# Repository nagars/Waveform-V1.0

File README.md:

# Waveform-V1.0 (May 2018 - August 2018)

## IMPORTANT NOTE
### **This project is incomplete.** 
Though all the peripherals have been implemented and tested, I abandoned compiling them all into one homogenous project. At the time my intention
was to revisit the core design and implement a version 2.0. The reasons why have been listed further down. Effectively, the only features missing are:

- The ability to select the required waveform from a menu on the LCD using the encoder
- The ability to select frequency of the signal via the encoder. [Removed because it was causing signal integrity issues]

## Inspiration
Back in May of 2018, fresh out of college I decided to gain some experience on the PIC24 line of MCU's. Microchip has good hobbyists support through forums and documentation. 
But the biggest reason was that their MCU's come in DIP packaging which meant I could just use a breadboard for prototyping. 

**This would become my first major embedded systems project and my first time working with a PIC outside of college. It would also be my second PCB design on EagleCAD. 
Please bear that in mind if you want to use this for reference.**

## Table of Contents
1. Objective
    1. Feature List
    2. Knowledge Base Required
2. Design Breakdown
    1. PIC MCU
    2. Rotary Encoder
    3. DAC
    4. DMA
    5. LCD
    6. Negative Voltage Generator
    7. Opamp Stage
    8. Voltage Regulator
3. Issues
4. Media
5. Future Scope

## Objective
The objective of this project was to make a Waveform Generator based on a PIC24. Signals to be generated included SINE, SAWTOOTH, SQUARE and TRIANGLE. 
The device would have to include Frequency, Amplitude and DC Offset adjustment. It was to run on a 12V power supply.

### Feature List

- Device should run on 12V power supply with a DC jack
- LCD screen to show which signal has been selected
- Encoder to select signal via LCD
- Encoder to set Frequency of signal
- Pushbutton to enable / disable signal output (Included within Encoder)
- MCU Debug interface for on board debugging
- Resistor Ladder based DAC implementation
- Amplitude adjustment to max +-10V
- Frequency adjustment to max 1Mhz
- Offset adjustment to max +-10V
- Power switch and LED indicator

## Knowledge Base Required

- MPLAB IDE

    MPLAB is microchips IDE for PIC and now several AVR MCU's. It has all the standard IDE features including project management and Debugging. Microchip has it's own HAL
    called Harmony. I deliberately chose not to use it as I wanted a deeper understanding of the PIC's features.
      
- C programming language

    A basic understanding of c is necessary. How to use For loops, switch cases etc.
    
- Microcontroller basics

    A basic knowledge of how MCU's work, their hardware peripherals, working of interrupts and understanding of communication protocols is necessary. A major part of working with any MCU is understanding how to read and write to registers, access hardware etc.
      
- Analog Circuit Design / Analog Signals

    Knowledge regarding various signal types will be necessary. How Frequency, Ampitude and DC Offset affect a signal. How Opamps work, Thevenin and Norton theorem's, Linear regulators etc.
    
- EagleCAD

    EagleCAD is a what I designed the PCB in. It's popular among hobbyists because the free version is only limited by board size and not by the number of nodes as is with Orcad PCB Designer for example. It's a good place to start if you're looking to learn PCB designing.
    
    
## Design Breakdown
I will breakdown the software and hardware for each sub-system of my design.

Layout:

Schematic:

### PIC MCU
I used the [PIC24FJ64GA002](https://www.microchip.com/wwwproducts/en/PIC24FJ64GA002). Given the simple requirements of this project, almost any mainstream MCU will do.
Primarily I prioritised the following:

- Enough GPIO's (12 for the DAC, 3 for encoder inputs, 3 for the shift register, 2 for the LCD)
- 1 SPI (For the LCD)
- Fast speed (This one goes up to 32Mhz with an internal clock + PLL)
- DIP packaging to make a novice's life easier

## Rotary Encoder
I decided to use a relative rotary encoder with an internal pushbutton. The intention was to use the rotary encoder to select the signal type along with it's various parameters. The inputs would be finalised by pressing the encoder button. A good resource for encoders can be found [here](https://howtomechatronics.com/tutorials/arduino/rotary-encoder-works-use-arduino/).

The pushbutton along with the encoder outputs were driven to input GPIO's. I poll the encoder outputs using timer1 triggering an interrupt every 10ms. 

Since the encoder and its pushbutton are mechanical in nature, debouncing is necessary. This is because when a button is pressed, the metal plates make contact and tend to bounce on a microscopic level. This causes jitter or noise on the data line. This jitter can cause unpredictable behaviour as the signal jumps between the logic high and logic low thresholds of the gpio. To prevent this, there are several methods categorised as software and hardware debouncing. More information can be found [here](https://hackaday.com/2015/12/09/embed-with-elliot-debounce-your-noisy-buttons-part-i/). I chose to use hardware debouncing by implementing a simple rc filter to filter high frequency noise.

My code logic is simple. I read both outputs and place them into a single variable. The 0th and 1st bits represent each signal respectively. I enter a switch case where I compare the current configuration to the last polled one. Depending on which output has changed first, I determine if the encoder was rotated clockwise or counter-clockwise.

## DAC
DAC stands for **Digital to Analog Converter**. In short, it converts a digital number to an analog signal whose voltage varies depending on the value of said number. Say your DAC is 8 bits, it can handle numbers between 0 to 255. A value of 255 will output Vmax where as 128 will output 0.5*Vmax. 

I did not use the inbuilt DAC. I wanted to build my own using an R - 2R resistor ladder. There is no benefit to this, absolutely none but I did it anyway just to see how good or bad the results would be. You can find a good resource on it [here](https://www.electronics-tutorials.ws/combination/r-2r-dac.html).

Note: Most standard resistors have an error of between 10% to 1%. I ordered those with 0.1% error as the DAC is heavily dependent on equal values amongst its resistors. 

I decided to create a lookup table for the signals. It is an array of values that generate your signal on your DAC when you parse through the array. There are a bunch of tools to make lookup tables [like](https://www.daycounter.com/Calculators/Sine-Generator-Calculator.phtml).

I assigned the DAC pins to PORTB. Then I used the DMA module to transfer the array to PORTB. More information on that below. Depending on which gpio was set or cleared, the DAC put out a certain value between 0 and 5V. 

R - 2R DAC:

## DMA
DMA stands for **Direct Memory Access**. Basically it is an effective way of transfering data from one memory address to another, one peripheral to memory address or one memory address to a peripheral. Depending on the MCU, you may even transfer data from one peripheral to another. The advantage of using the DMA is that the processor has no role in this transfer. As a result it can go ahead and do other tasks without wasting time and resources on a memory transfer. The DMA runs independent of the processor.

I used the DMA to transfer 256 bytes from a specific lookup table address to the PORTB address. Upon completion, the DMA would trigger an interrupt where in I would trigger the same DMA transaction again resulting in a repeating signal generated at the DAC. 

There is a fundemental flaw in this method. How do you control the frequency of the signal? Instead of changing the rate of transfer to the DAC, I decided to reduce the number of data points of the signal to increase the frequency of the signal. So say for a 1 hz signal I would put out all 256 data points from the lookup table, to increase frequency I would reduce the number of data points. I did this by changing how I traverse the array. I would increase the number of elements to increment by. Thus, at higher frequencies the signal would be completely compromised. Even for a novice, this was a bad idea.

My plan now is to use a timer to trigger a single DMA transfer of 1 element in the array. With each trigger of the timer interrupt, I send out the next element to the port of the DAC. Now, I can control the frequency by adjusting the timer. I also found an [application note](http://ww1.microchip.com/downloads/en/Appnotes/00003312A.pdf) that does the same with the addded functionality of using a potentiometer to control the frequency.

 ## LCD
 I used a standard 16x2 LCD interfaced with a parallel port in 8 bit mode. The user would use the rotary encoder to select a highlighted option on the screen. A blinking option would mean you could change that options value. A good resource for interfacing an LCD like this can be found [here](https://circuitdigest.com/microcontroller-projects/16x2-lcd-interfacing-with-pic-microcontroller).
 
It uses an 8 bit parallel port for communication with the MCU. The PIC DIP package does not have enough gpio pins for that so I interfaced it with a 74HC595 shift register. The shift register takes a serial input which I interface with the SPI peripheral on the MCU. More information on shift registers can be found [here](https://lastminuteengineers.com/74hc595-shift-register-arduino-tutorial/).
  
LCD + Shift Register:

 ## Negative Voltage Generator
  The negative voltage generator circuit uses an IC555 Timer IC along with a configuration of Diodes and Capacitors to maintain a steady negative voltage of -12V at the output. 
  
  An IC555 timer is a common IC used to generate an oscillating signal. To do that, I use it in an Astable mode. By configuring the resistors and capacitors, I set my duty cycle to 50% with an oscillating frequency of 144Hz. This then feeds into the capacitor and diode setup. Detailed information on this can be found [here](https://www.allaboutcircuits.com/projects/build-your-own-negative-voltage-generator/).

-12V Generator:

 ## Opamp Stage
  I use the LM6178 opamp IC which comes with 2 opamps in an inverting amplifier configuration. The first Opamp stage is designed to offset and amplify the Analog signal coming from the DAC. This signal ranges from 0 to 5V. After the first opamp stage, the output signal is inverted and ranges from -0.5 to 0.5V. The second stage is designed to allow for user adjusted offset and amplitude using potentiometers. The output of the second stage can range from roughly -10V to 10V with an offset of +-10V.
  
Opamp Stage 1 & 2:

 ## Voltage Regulator
  I use the LM2576 5V buck converter to generate the 5V line to power the MCU, IC's and LCD. As a result the system has 3 power rails: 12V, -12V and 5V.

## Issues
Given that this was my first major project, a whole host of issues were expected.

1. Diode D1 overlaps the R - 2R ladder.
2. Diodes D2 and D3 do not fit in the space I provided on the board.
3. The power Jack is too large to fit on the board.
4. Higher frequencies result in the signal getting distorted. Issue is probably a combination of building my own DAC and of how I adjust the frequency in code explained above.
5. LCD used just looks plain awful hanging off the board.
6. Very very poor frequency control. 

## Media

Amplitude + Offset Adjustment: https://www.youtube.com/watch?v=x8Yp53ENj-I

Frequency Adjustment: https://www.youtube.com/watch?v=95g6IoSVtfY

## Future Scope
For now, this project is on pause. Between work, family and other projects I don't have any immediate plans to work on a version 2.0. However, the changes I will make when I get back to it will probably involve:

1. Replacing the PIC with an STM32. It's faster with clock going as far up as 40Mhz, it executes one instruction per cycle unlike the PIC with 2. The biggest factor
is the cost. The Pickit 4 debugger is around 7000 rs while an STM32 Nucleo evaluation board with the mcu and debugger is less than 2000 rs.

2. It goes without saying that I will switch to SMD parts to help with form factor. 

3. Finally, I'll abandon the R - 2R ladder and use the internal DAC of the MCU. Or maybe an external one with more bits. 

4. Implement an external oscillator for the MCU to avoid using a PLL.

5. Potentially implement digital potentiometers for signal adjustment.

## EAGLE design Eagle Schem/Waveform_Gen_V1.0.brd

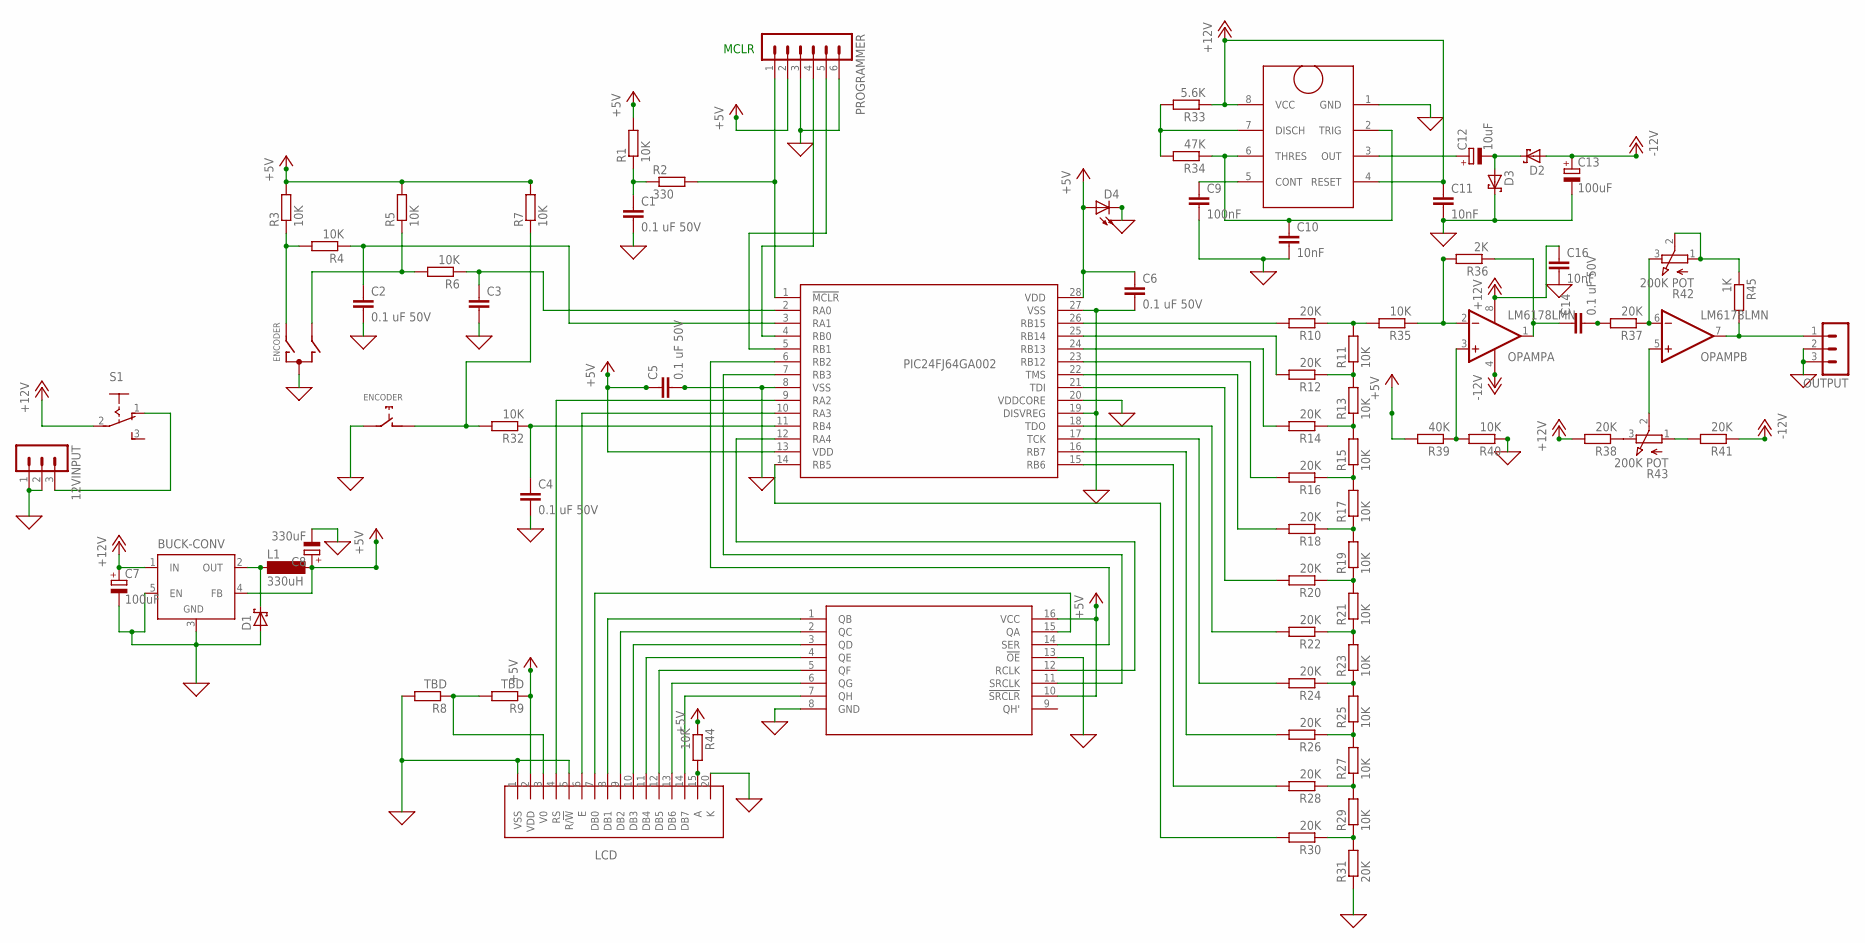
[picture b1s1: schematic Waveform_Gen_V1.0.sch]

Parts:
12VINPUT: MA03-1
BUCK-CONV: LM2596TH; TO220-52
C1, C2, C4, C5, C6, C14: 0.1 uF 50V; C5B2.5
C3: C5/2.5; C5B2.5
C7, C13: 100uF; E3,5-8
C8: 330uF; E3,5-10
C9: 100nF; C5B2.5
C10, C11, C16: 10nF; C5B2.5
C12: 10uF; E2,5-6E
D1, D2, D3: SCHOTTKY-DIODETO92H; TO92H
D4: SFH482
ENCODER: EC12E_SW; ALPS_EC12E_SW
IC555: IC555; DIL08
L1: 330uH; SD12K100
LCD: LCD_PIN; SIL16
OPAMP: LM6178LMN; DIL08
OUTPUT: MA03-1
PIC24FJ64GA002: PIC24FJ64GA002; DIL28-3
PROGRAMMER: MA06-1
R1, R3, R4, R5, R6, R7, R11, R13, R15, R17, R19, R21, R23, R25, R27, R29, R32, R35, R40, R44: 10K; 0207/10
R2: 330; 0207/10
R8, R9: TBD; 0207/10
R10, R12, R14, R16, R18, R20, R22, R24, R26, R28, R30, R31, R37, R38, R41: 20K; 0207/10
R33: 5.6K; 0207/10
R34: 47K; 0207/10
R36: 2K; 0207/10
R39: 40K; 0207/10
R42, R43: 200K POT; EVUF
R45: 1K; 0207/10
S1: 255SB
SHIFT-REG: 74HC595; DIL16

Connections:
+5V: BUCK-CONV.4 (FB), C5.1, C6.1, C8.+, D4.A, L1.2, LCD.2 (VDD), PIC24FJ64GA002.13 (VDD), PIC24FJ64GA002.28 (VDD), PROGRAMMER.2, R1.2, R3.2, R5.2, R7.2, R9.1, R39.2, R44.1, SHIFT-REG.10 (!SRCLR), SHIFT-REG.16 (VCC)
+12V: BUCK-CONV.1 (IN), C7.+, C11.1, C16.1, IC555.4 (RESET), IC555.8 (VCC), OPAMP.8 (V+), R33.1, R38.2, S1.2
-12V: C13.+, D2.1 (A), OPAMP.4 (V-), R41.1
GND: 12VINPUT.1, 12VINPUT.2, BUCK-CONV.3 (GND), BUCK-CONV.5 (EN), C1.2, C2.2, C3.2, C4.2, C5.2, C6.2, C7.-, C8.-, C9.2, C10.2, C11.2, C13.-, C16.2, D1.1 (A), D3.2 (C), D4.K (C), ENCODER.C, ENCODER.E (2), IC555.1 (GND), LCD.1 (VSS), LCD.5 (R/!W), LCD.20 (K), OUTPUT.2, OUTPUT.3, PIC24FJ64GA002.8 (VSS), PIC24FJ64GA002.19 (DISVREG), PIC24FJ64GA002.20 (VDDCORE), PIC24FJ64GA002.27 (VSS), PROGRAMMER.3, PROGRAMMER.6, R8.2, R31.1, R40.1, SHIFT-REG.8 (GND), SHIFT-REG.13 (!OE)
unnamed: PIC24FJ64GA002.7 (RB3), SHIFT-REG.11 (SRCLK)
unnamed: PIC24FJ64GA002.6 (RB2), SHIFT-REG.14 (SER)
unnamed: PIC24FJ64GA002.12 (RA4), SHIFT-REG.12 (RCLK)
unnamed: R42.1 (A), R42.2 (S), R45.1
unnamed: C3.1, PIC24FJ64GA002.2 (RA0), R6.1
unnamed: ENCODER.A, R3.1, R4.2
unnamed: PIC24FJ64GA002.1 (!MCLR), PROGRAMMER.1, R2.2
unnamed: C1.1, R1.1, R2.1
unnamed: ENCODER.D (1), R7.1, R32.2
unnamed: PIC24FJ64GA002.26 (RB15), R10.2
unnamed: C2.1, PIC24FJ64GA002.3 (RA1), R4.1
unnamed: ENCODER.B, R5.1, R6.2
unnamed: C4.1, PIC24FJ64GA002.11 (RB4), R32.1
unnamed: PIC24FJ64GA002.4 (RB0), PROGRAMMER.4
unnamed: PIC24FJ64GA002.5 (RB1), PROGRAMMER.5
unnamed: R10.1, R11.2, R35.2
unnamed: PIC24FJ64GA002.25 (RB14), R12.2
unnamed: R11.1, R12.1, R13.2
unnamed: R13.1, R14.1, R15.2
unnamed: R15.1, R16.1, R17.2
unnamed: R17.1, R18.1, R19.2
unnamed: R19.1, R20.1, R21.2
unnamed: R21.1, R22.1, R23.2
unnamed: R23.1, R24.1, R25.2
unnamed: R25.1, R26.1, R27.2
unnamed: R27.1, R28.1, R29.2
unnamed: R29.1, R30.1, R31.2
unnamed: PIC24FJ64GA002.24 (RB13), R14.2
unnamed: PIC24FJ64GA002.23 (RB12), R16.2
unnamed: PIC24FJ64GA002.22 (TMS), R18.2
unnamed: PIC24FJ64GA002.21 (TDI), R20.2
unnamed: PIC24FJ64GA002.18 (TDO), R22.2
unnamed: PIC24FJ64GA002.17 (TCK), R24.2
unnamed: PIC24FJ64GA002.16 (RB7), R26.2
unnamed: PIC24FJ64GA002.15 (RB6), R28.2
unnamed: LCD.7 (DB0), SHIFT-REG.15 (QA)
unnamed: PIC24FJ64GA002.14 (RB5), R30.2
unnamed: LCD.8 (DB1), SHIFT-REG.1 (QB)
unnamed: LCD.9 (DB2), SHIFT-REG.2 (QC)
unnamed: LCD.10 (DB3), SHIFT-REG.3 (QD)
unnamed: LCD.11 (DB4), SHIFT-REG.4 (QE)
unnamed: LCD.12 (DB5), SHIFT-REG.5 (QF)
unnamed: LCD.13 (DB6), SHIFT-REG.6 (QG)
unnamed: LCD.14 (DB7), SHIFT-REG.7 (QH)
unnamed: LCD.3 (V0), R8.1, R9.2
unnamed: LCD.4 (RS), PIC24FJ64GA002.9 (RA2)
unnamed: LCD.6 (E), PIC24FJ64GA002.10 (RA3)
unnamed: BUCK-CONV.2 (OUT), D1.2 (C), L1.1
unnamed: LCD.15 (A), R44.2
unnamed: C10.1, IC555.2 (TRIG), IC555.6 (THRES), R34.1
unnamed: C12.-, D2.2 (C), D3.1 (A)
unnamed: C9.1, IC555.5 (CONT)
unnamed: IC555.7 (DISCH), R33.2, R34.2
unnamed: C12.+, IC555.3 (OUT)
unnamed: OPAMP.2 (-IN), R35.1, R36.2
unnamed: C14.1, OPAMP.1 (OUT), R36.1
unnamed: OPAMP.3 (+IN), R39.1, R40.2
unnamed: OPAMP.6 (-IN), R37.1, R42.3 (E)
unnamed: R38.1, R43.3 (E)
unnamed: OPAMP.7 (OUT), OUTPUT.1, R45.2
unnamed: OPAMP.5 (+IN), R43.2 (S)
unnamed: R41.2, R43.1 (A)
unnamed: 12VINPUT.3, S1.1 (O)
unnamed: C14.2, R37.2

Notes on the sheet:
MCLR

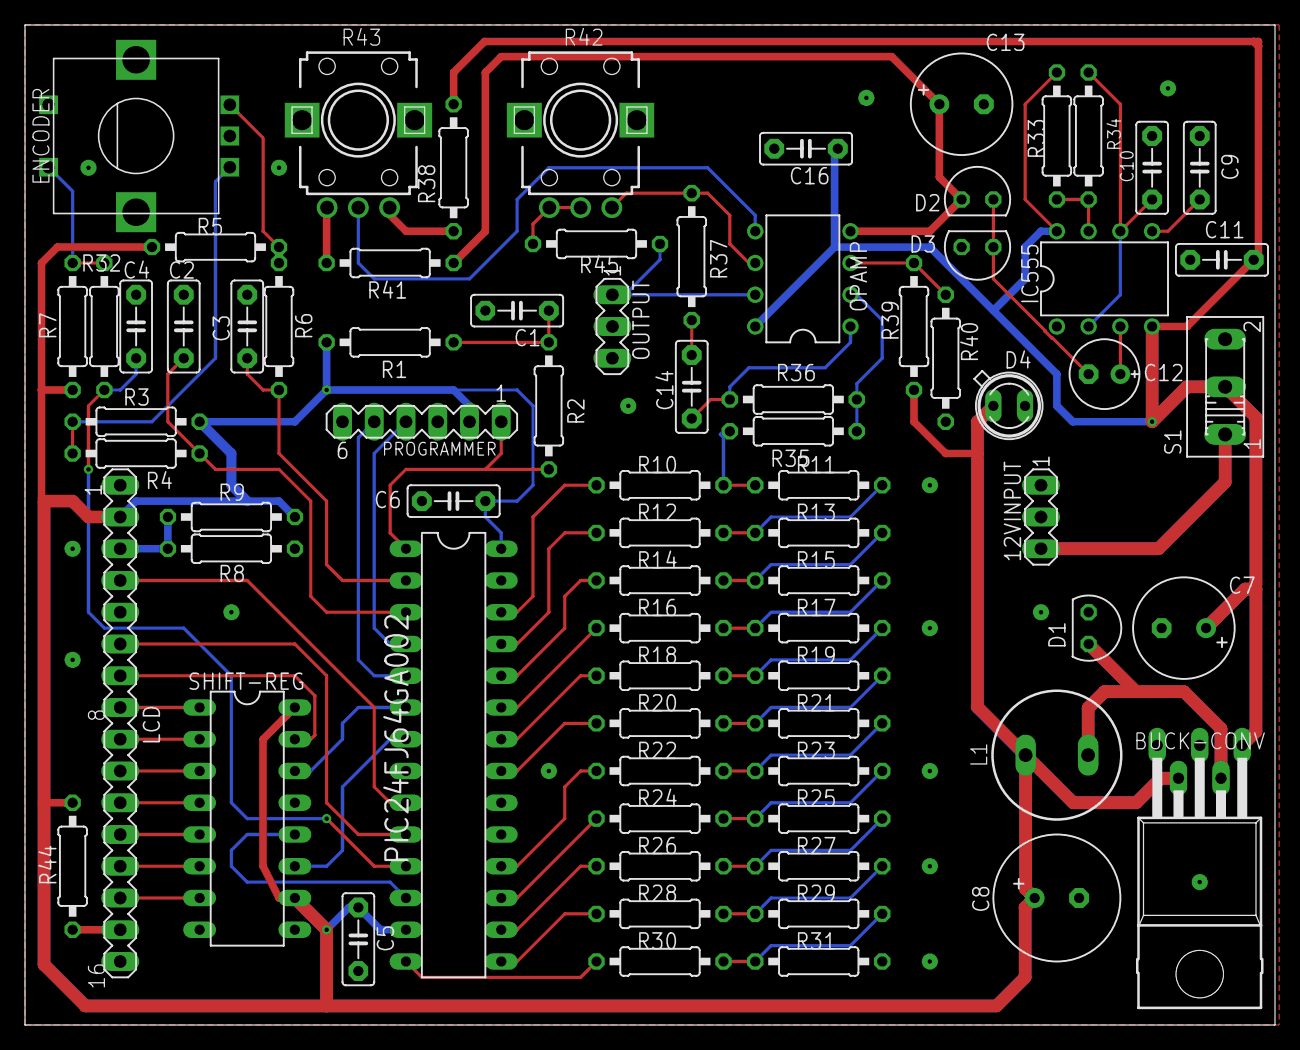
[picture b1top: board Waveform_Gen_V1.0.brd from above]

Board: 2 copper layers, 100.0 x 80.0 mm, 76 parts (0 on the bottom side), 68 nets.

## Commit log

2019-06-25 Add files via upload
    Waveform Generator First Iteration. Built in the summer of 2018.
2021-01-02 Cleaned up Repository, adjusted directories to make it more legible
2021-01-02 Create README.md
    Unfinished. To be completed.
2021-01-04 Updated Readme file
2021-03-21 Final cleaning up of uneeded files
